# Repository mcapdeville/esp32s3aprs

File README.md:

# ESP32s3APRS

The ESP32s3APRS project aims to develop an open-source APRS (Automatic Packet Reporting System) beacon/tracker/logger, USB kiss TNC , USB audio FM tranceiver with Micropython shell based on the ESP32-S3 microcontroller.

## Project Overview

The ESP32s3APRS is a comprehensive solution that combines hardware and software components to create a versatile packet radio. The main features include:

- **APRS and AX.25 Capabilities**: The device can transmit and receive APRS and AX.25 frames, allowing for bidirectional communication over radio.
- **USB Connectivity**: The tracker connects to a computer via USB, providing two CDC-ACM ports:
  - One port for a TNC KISS protocol interface
  - One port for a MicroPython console
- **UAC2 Audio Support**: The USB implementation includes the UAC2 protocol, enabling direct audio streaming between the device and the computer.
- **GPS**: Integrated GPS with embeded antenna.
- **Sensor Integration**: The tracker can integrate various sensors, to enrich the data transmitted over the APRS network.
- **USB-C battery charger**: can accept power input from 5v to 14V 
- **User Interface**: The device features an e-paper display and three buttons for configuration and control.
- **Power Management**: The system is designed for low power consumption, allowing for extended autonomous operation.

## Hardware Components

The ESP32s3APRS hardware consists of the following main components:

- ESP32-S3 microcontroller
- SA868 radio module
- Quectel L86 GPS receiver
- E-paper display
- 3 buttons
- USB-C battery charger

The schematic and PCB are designed with Kicad (https://www.kicad.org).
The hardware design files are distributed under the CERN-OHL-S v2 license (or later)

## Software

The software for the ESP32s3APRS is released under the GPL v3 (or later) license. It includes:

- Embedded firmware for the ESP32-S3
- APRS and AX.25 frame processing
- Data storage in flash memory
- Configuration via the user interface and MicroPython console

## Getting Started

To get started with the ESP32s3APRS project, please follow these steps:

1. Clone the repository: `git clone https://github.com/mcapdeville/esp32s3aprs.git`
2. Change to project directory: cd esp32s3aprs
3. Initialize submodules : ./init.sh

## Compile

From the project directory :

1. Load the environment variables: . ./esp-idf/export.sh
2. Compile the project: idf.py build

## Flash the device

1. Put the switch on 'Boot' position
2. Connect USB cable
3. Run: idf.py flash

## Contributing

The ESP32s3APRS project welcomes contributions from the community. You can contribute by:

- Reporting bugs or issues
- Suggesting new features or improvements
- Submitting pull requests for code or documentation changes

## License

The ESP32s3APRS software is licensed under the GPL v3 (or later) license.
The hardware design files are licensed under the CERN-OHL-S v2 license.
See the `LICENSE-GPL-V3.txt` and `LICENSE-CERN-OHL-S-V2.txt` files for more details.

## Acknowledgments

The ESP32s3APRS project was created by Marc CAPDEVILLE (F4JMZ).

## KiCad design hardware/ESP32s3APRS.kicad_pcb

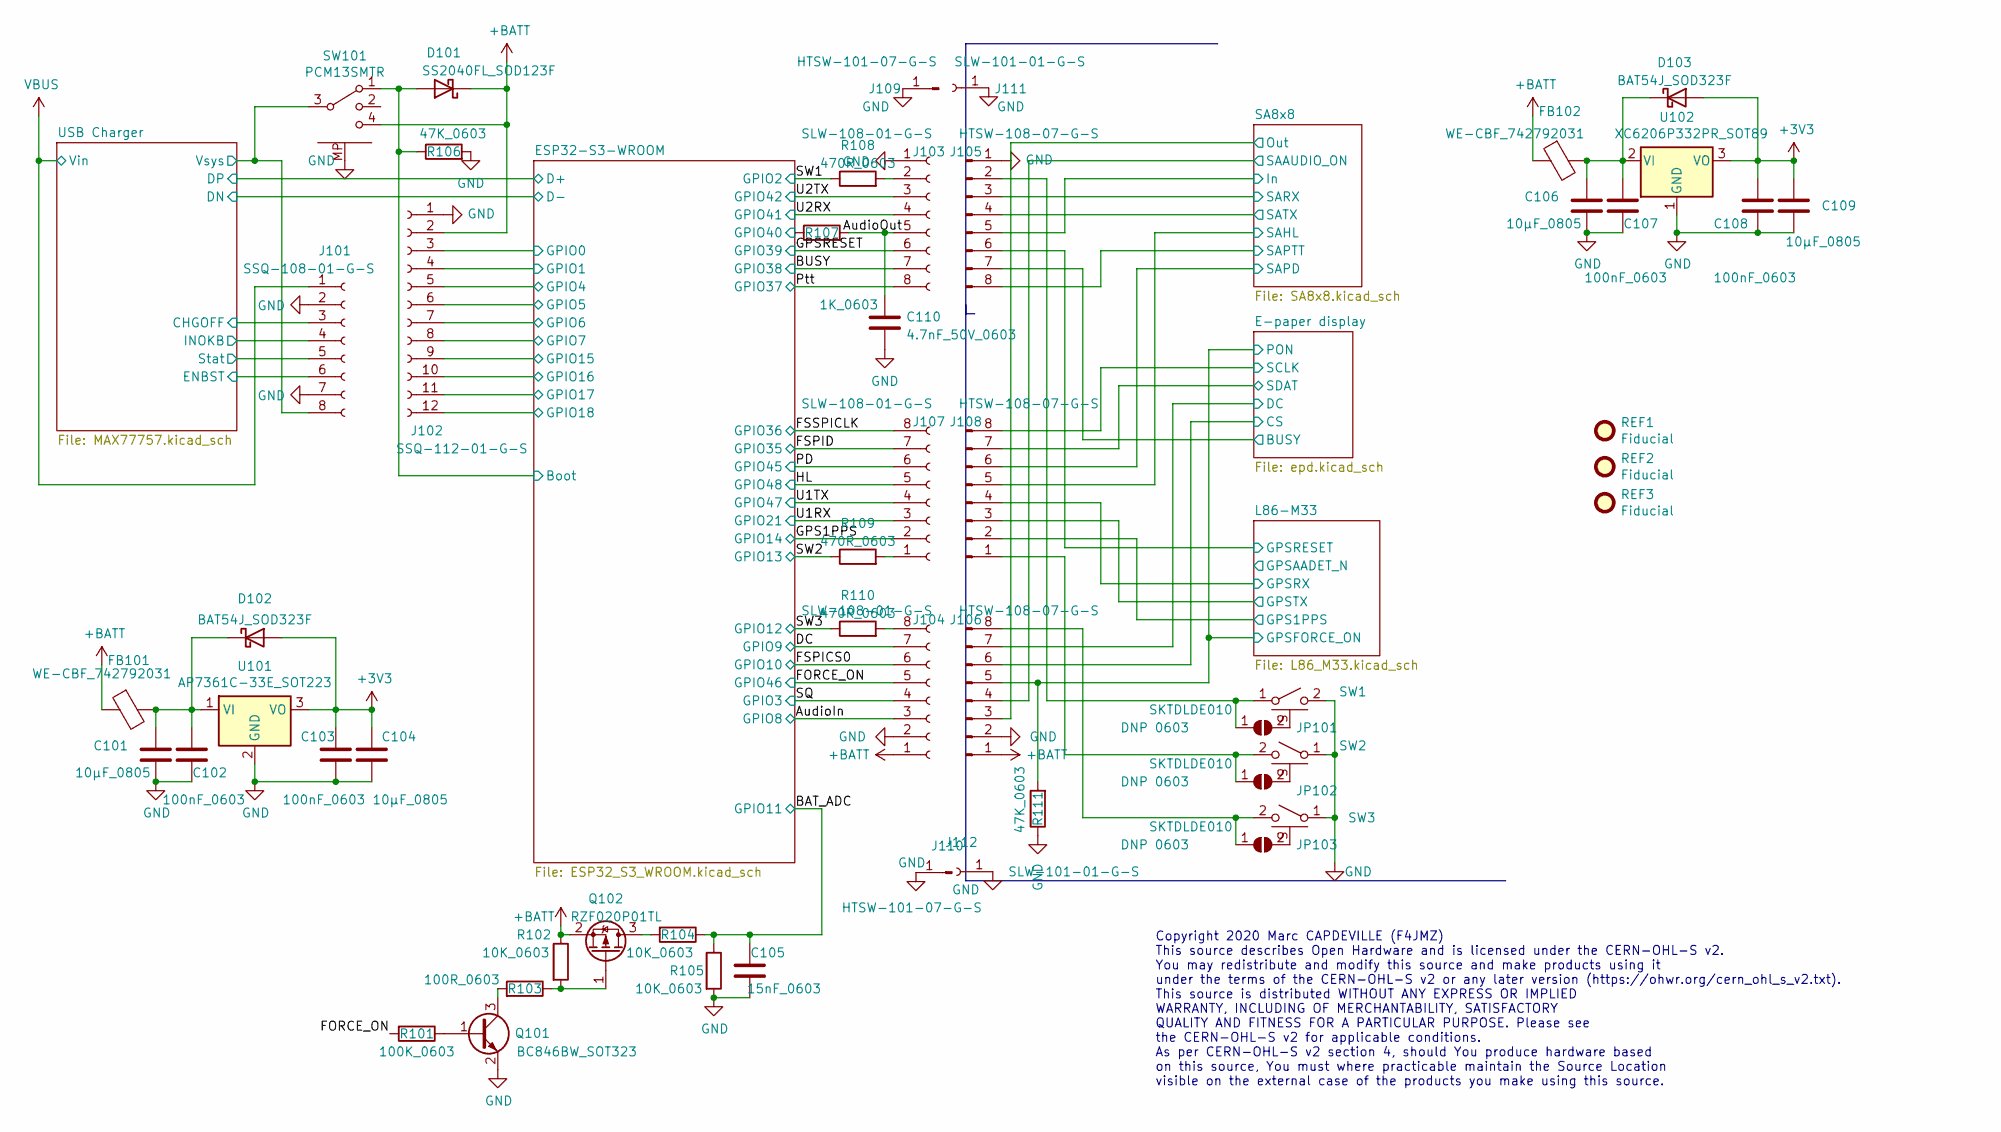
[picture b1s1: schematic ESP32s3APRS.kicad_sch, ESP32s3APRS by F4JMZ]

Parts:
C101, C104, C106, C109: 10µF_0805; C_0805_2012Metric; Mouser 963-TMK212BBJ106MG-T
C102, C103, C107, C108: 100nF_0603; C_0603_1608Metric; Mouser 963-UMK107B7104KAHT
C105: 15nF_0603; C_0603_1608Metric; Mouser 710-885012206090
C110: 4.7nF_50V_0603; C_0603_1608Metric; Mouser 80-C0603C472K5R
D101: SS2040FL_SOD123F; D_SOD-123F; Mouser 241-SS2040FLAUR100A1
D102, D103: BAT54J_SOD323F; D_SOD-323F; Mouser 771-BAT54J115
FB101, FB102: WE-CBF_742792031; L_0805_2012Metric; Mouser 710-742792031
J101: SSQ-108-01-G-S; PinSocket_1x08_P2.54mm_Vertical; Mouser 200-SSQ10801GS
J102: SSQ-112-01-G-S; PinSocket_1x12_P2.54mm_Vertical; Mouser 200-SSQ11201GS
J103, J104, J107: SLW-108-01-G-S; PinSocket_1x08_P2.54mm_Vertical; Mouser 200-SLW10801GS
J105, J106, J108: HTSW-108-07-G-S; PinHeader_1x08_P2.54mm_Vertical; Mouser 200-HTSW10807GS
J109, J110: HTSW-101-07-G-S; PinHeader_1x01_P2.54mm_Vertical; Mouser 200-HTSW10107GS
J111, J112: SLW-101-01-G-S; PinSocket_1x01_P2.54mm_Vertical; Mouser 200-SLW10101GS
JP101, JP102, JP103: DNP 0603; R_0603_1608Metric_Pad0.98x0.95mm_HandSolder
Q101: BC846BW_SOT323; SOT-323_SC-70; Mouser 771-BC846BW-T/R
Q102: RZF020P01TL; SOT-323T_SC-113A; Mouser 755-RZF020P01TL
R101: 100K_0603; R_0603_1608Metric; Mouser 603-RC0603FR-07100KL
R102, R104, R105: 10K_0603; R_0603_1608Metric; Mouser 603-RC0603FR-0710KL
R103: 100R_0603; R_0603_1608Metric; Mouser 603-RC0603FR-07100RL
R106, R111: 47K_0603; R_0603_1608Metric; Mouser 603-RC0603FR-0747KL
R107: 1K_0603; R_0603_1608Metric; Mouser 603-RC0603FR-071KL
R108, R109, R110: 470R_0603; R_0603_1608Metric
REF1, REF2, REF3: Fiducial; Fiducial_0.75mm_Mask1.5mm
SW1, SW2, SW3: SKTDLDE010; Mouser 688-SKTDLDE010
SW101: PCM13SMTR; SW_PCM13SMTR _SP3T; Mouser 611-PCM13SMTR
U101: AP7361C-33E_SOT223; SOT-223-3_TabPin2; Mouser 621-AP7361C-33E-13
U102: XC6206P332PR_SOT89; SOT-89-3; Mouser 865-XC6206P332PR-G

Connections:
+3V3: C103.1, C104.1, C108.1, C109.1, D102.2 (A), D103.2 (A), U101.3 (VO), U102.3 (VO); also elsewhere on the board
+BATT: D101.1 (K), FB101.1, FB102.1, J102.2, J104.1, J106.1, Q102.2 (S), R102.1, SW101.4; also elsewhere on the board
/AudioIn: J104.3; also elsewhere on the board
/BAT_ADC: C105.1, R104.1, R105.1; also elsewhere on the board
/BUSY: J103.7; also elsewhere on the board
/DC: J104.7; also elsewhere on the board
/E-paper display/BUSY: J105.7; also elsewhere on the board
/E-paper display/CS: J106.6; also elsewhere on the board
/E-paper display/DC: J106.7; also elsewhere on the board
/E-paper display/PON: J106.5, R111.2; also elsewhere on the board
/E-paper display/SCLK: J108.8; also elsewhere on the board
/E-paper display/SDAT: J108.7; also elsewhere on the board
/ESP32-S3-WROOM/Boot: D101.2 (A), R106.1, SW101.1; also elsewhere on the board
/ESP32-S3-WROOM/GPIO0: J102.3; also elsewhere on the board
/ESP32-S3-WROOM/GPIO1: J102.4; also elsewhere on the board
/ESP32-S3-WROOM/GPIO4: J102.5; also elsewhere on the board
/ESP32-S3-WROOM/GPIO5: J102.6; also elsewhere on the board
/ESP32-S3-WROOM/GPIO6: J102.7; also elsewhere on the board
/ESP32-S3-WROOM/GPIO7: J102.8; also elsewhere on the board
/ESP32-S3-WROOM/GPIO15: J102.9; also elsewhere on the board
/ESP32-S3-WROOM/GPIO16: J102.10; also elsewhere on the board
/ESP32-S3-WROOM/GPIO17: J102.11; also elsewhere on the board
/ESP32-S3-WROOM/GPIO18: J102.12; also elsewhere on the board
/ESP32-S3-WROOM/GPIO40: R107.1; also elsewhere on the board
/FORCE_ON: J104.5, R101.2; also elsewhere on the board
/FSPICS0: J104.6; also elsewhere on the board
/FSPID: J107.7; also elsewhere on the board
/FSSPICLK: J107.8; also elsewhere on the board
/GPS1PPS: J107.2; also elsewhere on the board
/GPSRESET: J103.6; also elsewhere on the board
/HL: J107.5; also elsewhere on the board
/L86-M33/GPS1PPS: J108.2; also elsewhere on the board
/L86-M33/GPSRESET: J105.6; also elsewhere on the board
/L86-M33/GPSRX: J108.4; also elsewhere on the board
/L86-M33/GPSTX: J108.3; also elsewhere on the board
/PD: J107.6; also elsewhere on the board
/Ptt: J103.8; also elsewhere on the board
/SA8x8/In: J105.5; also elsewhere on the board
/SA8x8/Out: J106.3; also elsewhere on the board
/SA8x8/SAAUDIO_ON: J106.4; also elsewhere on the board
/SA8x8/SAHL: J108.5; also elsewhere on the board
/SA8x8/SAPD: J108.6; also elsewhere on the board
/SA8x8/SAPTT: J105.8; also elsewhere on the board
/SA8x8/SARX: J105.3; also elsewhere on the board
/SA8x8/SATX: J105.4; also elsewhere on the board
/SQ: J104.4; also elsewhere on the board
/SW1: R108.1; also elsewhere on the board
/SW2: R109.1; also elsewhere on the board
/SW3: R110.1; also elsewhere on the board
/U1RX: J107.3; also elsewhere on the board
/U1TX: J107.4; also elsewhere on the board
/U2RX: J103.4; also elsewhere on the board
/U2TX: J103.3; also elsewhere on the board
/USB Charger/CHGOFF: J101.3; also elsewhere on the board
/USB Charger/ENBST: J101.6; also elsewhere on the board
/USB Charger/INOKB: J101.4; also elsewhere on the board
/USB Charger/Stat: J101.5; also elsewhere on the board
/USB Charger/Vsys: J101.8, SW101.3; also elsewhere on the board
GND: C101.2, C102.2, C103.2, C104.2, C105.2, C106.2, C107.2, C108.2, C109.2, C110.2, J101.2, J101.7, J102.1, J103.1, J104.2, J105.1, J106.2, J109.1, J110.1, J111.1, J112.1, Q101.2 (E), R105.2, R106.2, R111.1, SW1.2 (B), SW2.1 (A), SW3.1 (A), SW101.MP, U101.2 (GND), U102.1 (GND); also elsewhere on the board
unnamed: C101.1, C102.1, D102.1 (K), FB101.2, U101.1 (VI)
unnamed: C106.1, C107.1, D103.1 (K), FB102.2, U102.2 (VI)
unnamed: C110.1, J103.5, R107.2
unnamed: J103.2, R108.2
unnamed: J104.8, R110.2
unnamed: J105.2, JP101.1 (A), SW1.1 (A)
unnamed: J106.8, JP103.1 (A), SW3.2 (B)
unnamed: J107.1, R109.2
unnamed: J108.1, JP102.1 (A), SW2.2 (B)
unnamed: JP101.2 (B), SW1.S (MP)
unnamed: JP102.2 (B), SW2.S (MP)
unnamed: JP103.2 (B), SW3.S (MP)
unnamed: Q101.1 (B), R101.1
unnamed: Q101.3 (C), R103.2
unnamed: Q102.1 (G), R102.2, R103.1
unnamed: Q102.3 (D), R104.2
VBUS: J101.1; also elsewhere on the board

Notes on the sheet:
Copyright 2020 Marc CAPDEVILLE (F4JMZ) This source describes Open Hardware and is licensed under the CERN-OHL-S v2. You may redistribute and modify this source and make products using it under the terms of the CERN-OHL-S v2 or any later version (https://ohwr.org/cern_ohl_s_v2.txt). This source is d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

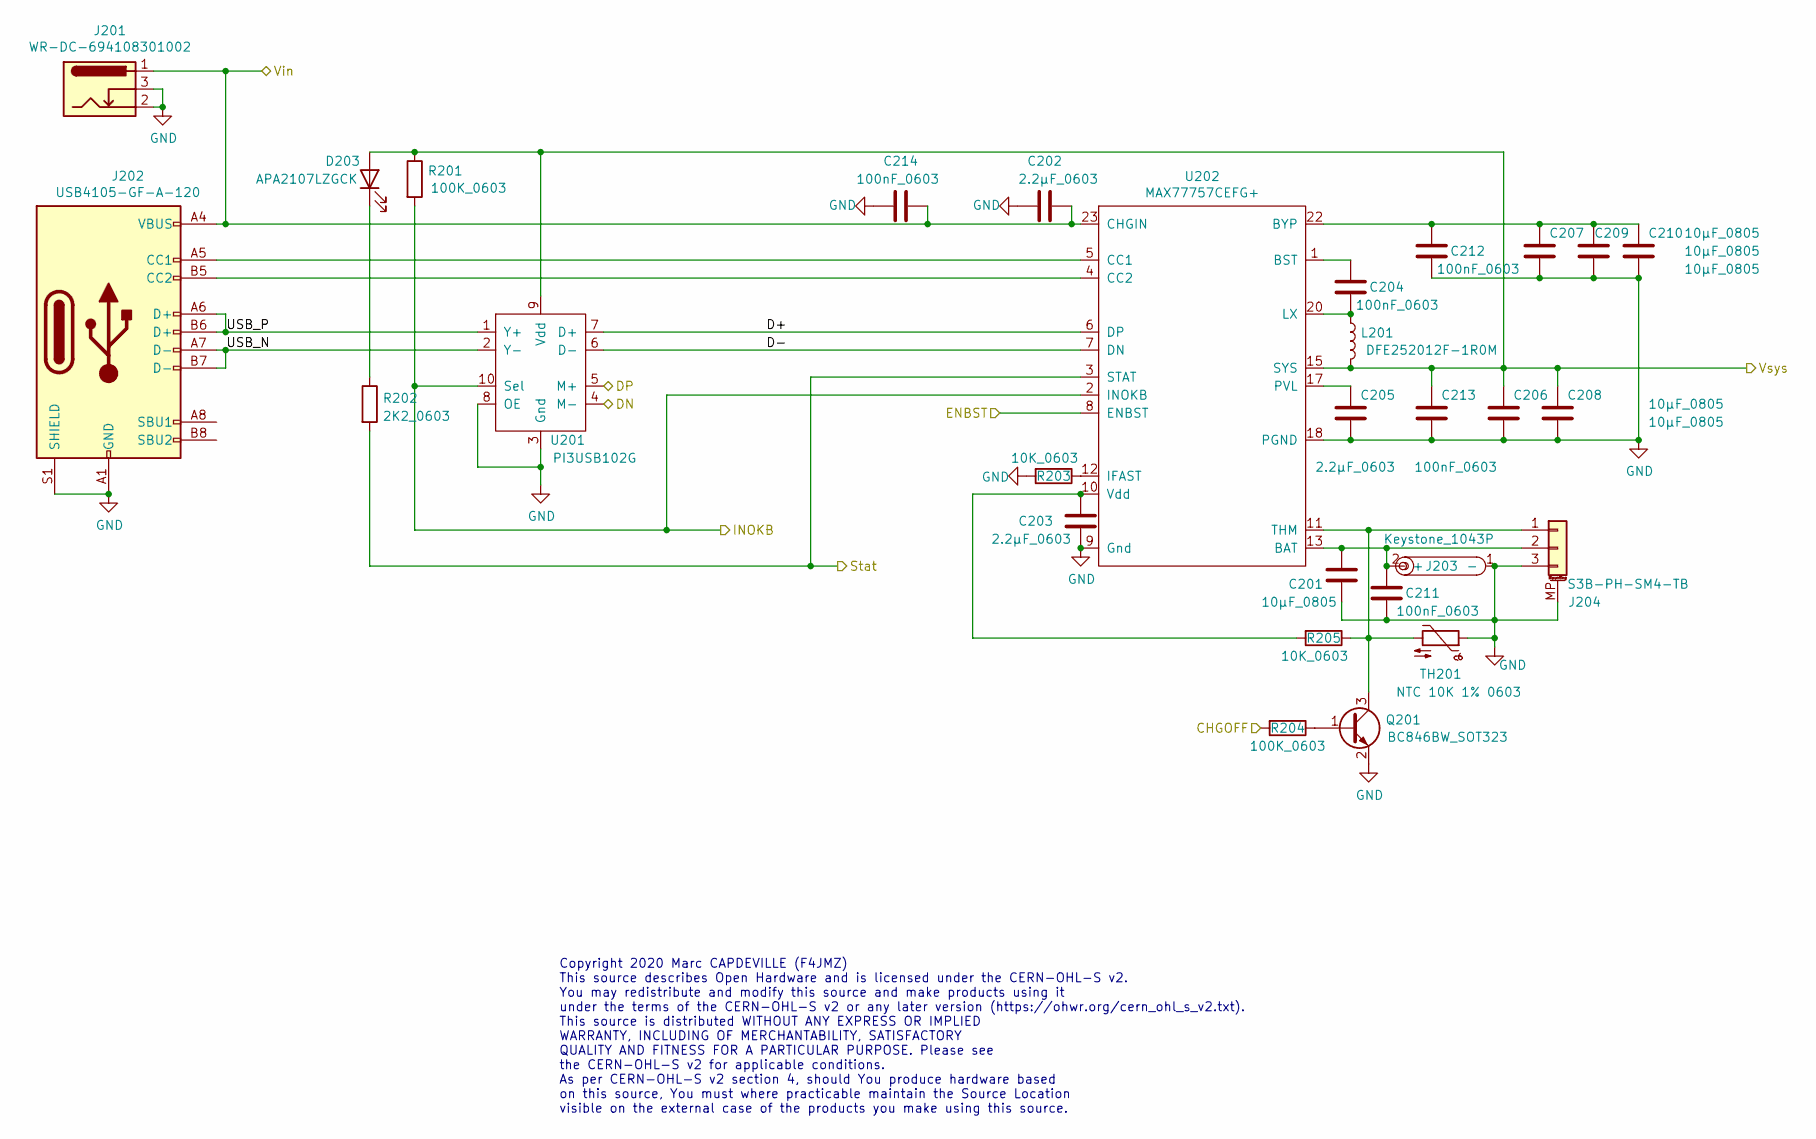
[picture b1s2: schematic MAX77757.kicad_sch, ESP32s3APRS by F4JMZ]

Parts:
C201, C206, C207, C208, C209, C210: 10µF_0805; C_0805_2012Metric; Mouser 963-TMK212BBJ106MG-T
C202, C203, C205: 2.2µF_0603; C_0603_1608Metric; Mouser 963-UMK107BBJ225KA-T
C204, C211, C212, C213, C214: 100nF_0603; C_0603_1608Metric; Mouser 963-UMK107B7104KAHT
D203: APA2107LZGCK; SIDELED_APA2107; Mouser 604-APA2107LZGCK
J201: WR-DC-694108301002; BarrelJack_Wuerth_6941xx301002; Mouser 710-694108301002
J202: USB4105-GF-A-120; USB_C_Receptacle_GCT_4105; Mouser 640-USB4105-GF-A-120
J203: Keystone_1043P; Keystone-1043; Mouser 534-1043
J204: S3B-PH-SM4-TB; JST_PH_S3B-PH-SM4-TB_1x03-1MP_P2.00mm_Horizontal; Mouser 306-S3BPHSM4TBLFSN
L201: DFE252012F-1R0M; L_1008_2520Metric; Mouser 81-DFE252012F-1R0MP2
Q201: BC846BW_SOT323; SOT-323_SC-70; Mouser 771-BC846BW-T/R
R201, R204: 100K_0603; R_0603_1608Metric; Mouser 603-RC0603FR-07100KL
R202: 2K2_0603; R_0603_1608Metric; Mouser 603-RC0603FR-072K2L
R203, R205: 10K_0603; R_0603_1608Metric; Mouser 603-RC0603FR-0710KL
TH201: NTC 10K 1% 0603; R_0603_1608Metric; Mouser 594-NTCS0603E3103FMT
U201: PI3USB102G; TQFN-10_1.3x1.6mm_P0.4mm; Mouser 729-PI3USB102GZLEX
U202: MAX77757CEFG+; FC2QFN-24_3x3_Pitch0.4mm; Mouser 700-MAX77757JEFG420

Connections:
/ESP32-S3-WROOM/D+: U201.5 (M+); also elsewhere on the board
/ESP32-S3-WROOM/D-: U201.4 (M-); also elsewhere on the board
/USB Charger/CHGOFF: R204.2; also elsewhere on the board
/USB Charger/D+: U201.7 (D+), U202.6 (DP)
/USB Charger/D-: U201.6 (D-), U202.7 (DN)
/USB Charger/ENBST: U202.8 (ENBST); also elsewhere on the board
/USB Charger/INOKB: R201.2, U201.10 (Sel), U202.2 (INOKB); also elsewhere on the board
/USB Charger/Stat: R202.2, U202.3 (STAT); also elsewhere on the board
/USB Charger/USB_N: J202.A7 (D-), J202.B7 (D-), U201.2 (Y-)
/USB Charger/USB_P: J202.A6 (D+), J202.B6 (D+), U201.1 (Y+)
/USB Charger/Vsys: C206.1, C208.1, C213.1, D203.2 (A), L201.2, R201.1, U201.9 (Vdd), U202.15 (SYS), U202.16 (SYS); also elsewhere on the board
GND: C201.2, C202.2, C203.2, C205.2, C206.2, C207.2, C208.2, C209.2, C210.2, C211.2, C212.2, C213.2, C214.2, J201.2, J201.3, J202.A1 (GND), J202.A12 (GND), J202.B1 (GND), J202.B12 (GND), J202.S1 (SHIELD), J203.1 (-), J204.3, J204.MP (MountPin), Q201.2 (E), R203.2, TH201.1, U201.3 (Gnd), U201.8 (OE), U202.9 (Gnd), U202.18 (PGND), U202.19 (PGND); also elsewhere on the board
unnamed: C201.1, C211.1, J203.2 (+), J204.2, U202.13 (BAT), U202.14 (BAT)
unnamed: C203.1, R205.2, U202.10 (Vdd)
unnamed: C204.1, U202.1 (BST)
unnamed: C204.2, L201.1, U202.20 (LX), U202.21 (LX)
unnamed: C205.1, U202.17 (PVL)
unnamed: C207.1, C209.1, C210.1, C212.1, U202.22 (BYP)
unnamed: D203.1 (K), R202.1
unnamed: J202.A5 (CC1), U202.5 (CC1)
unnamed: J202.B5 (CC2), U202.4 (CC2)
unnamed: J204.1, Q201.3 (C), R205.1, TH201.2, U202.11 (THM)
unnamed: Q201.1 (B), R204.1
unnamed: R203.1, U202.12 (IFAST)
VBUS: C202.1, C214.1, J201.1, J202.A4 (VBUS), J202.A9 (VBUS), J202.B4 (VBUS), J202.B9 (VBUS), U202.23 (CHGIN), U202.24 (CHGIN); also elsewhere on the board

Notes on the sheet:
Copyright 2020 Marc CAPDEVILLE (F4JMZ) This source describes Open Hardware and is licensed under the CERN-OHL-S v2. You may redistribute and modify this source and make products using it under the terms of the CERN-OHL-S v2 or any later version (https://ohwr.org/cern_ohl_s_v2.txt). This source is d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

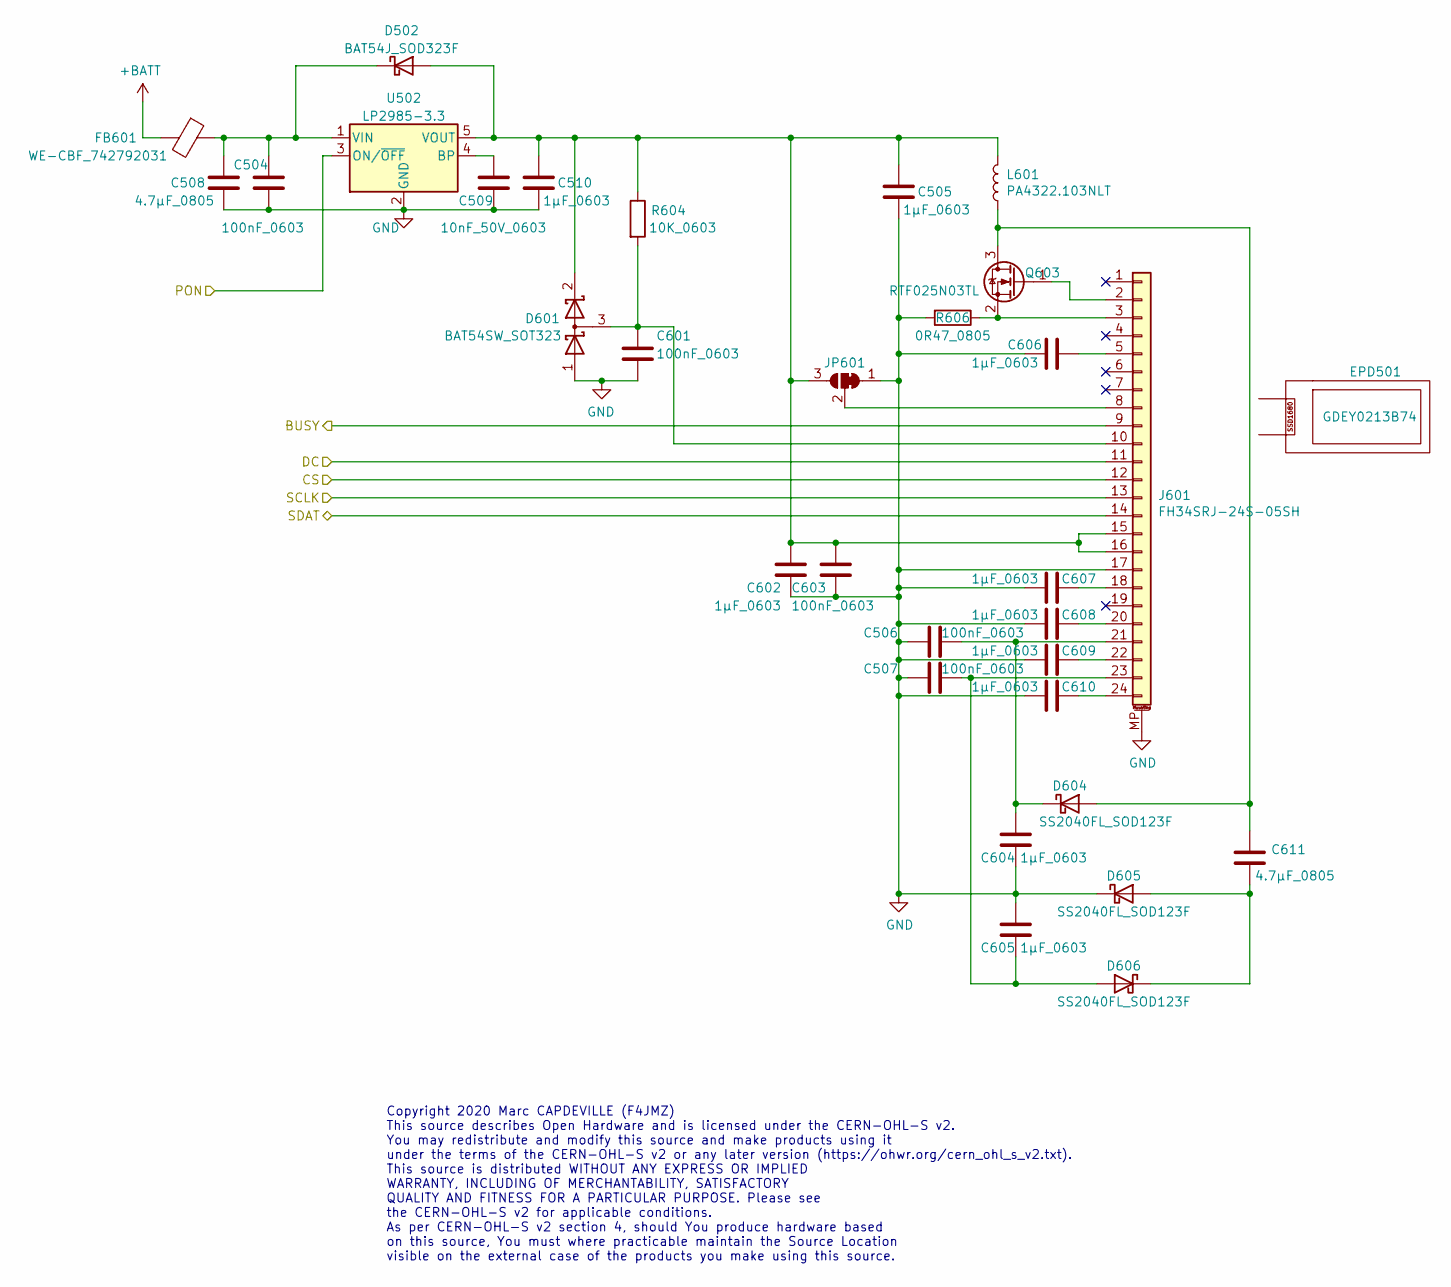
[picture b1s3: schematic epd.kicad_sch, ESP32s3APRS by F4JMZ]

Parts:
C504, C506, C507, C601, C603: 100nF_0603; C_0603_1608Metric; Mouser 963-UMK107B7104KAHT
C505, C510, C602, C604, C605, C606, C607, C608, C609, C610: 1µF_0603; C_0603_1608Metric; Mouser 963-UMK107BJ105KA-T
C508, C611: 4.7µF_0805; C_0805_2012Metric; Mouser 81-GRM21BR61H475KE1L
C509: 10nF_50V_0603; C_0603_1608Metric
D502: BAT54J_SOD323F; D_SOD-323F; Mouser 771-BAT54J115
D601: BAT54SW_SOT323; SOT-323_SC-70; Mouser 771-BAT54SW-T/R
D604, D605, D606: SS2040FL_SOD123F; D_SOD-123F; Mouser 241-SS2040FLAUR100A1
EPD501: GDEY0213B74; GDEY0213B74_2.13_EPD
FB601: WE-CBF_742792031; L_0805_2012Metric; Mouser 710-742792031
J601: FH34SRJ-24S-05SH; Hirose_FH34-24SRJ-0.5SH_1x24-1MP_P0.50mm_Horizontal; Mouser 798-FH34SRJ24S05SH99
JP601: SolderJumper_3_Bridged12; SolderJumper-3_P1.3mm_Bridged2Bar12_Pad1.0x1.5mm_NumberLabe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
L601: PA4322.103NLT; Inductor_Pulse_PA4322.xxxNLT_5.1x5.1; Mouser 673-PA4322.103NLT
Q603: RTF025N03TL; SOT-323T_SC-113A; Mouser 755-RTF025N03TL
R604: 10K_0603; R_0603_1608Metric; Mouser 603-RC0603FR-0710KL
R606: 0R47_0805; R_0805_2012Metric; Mouser 71-RCWE0805R470FKEA
U502: LP2985-3.3; SOT-23-5

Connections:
+BATT: FB601.2; also elsewhere on the board
/E-paper display/BUSY: J601.9; also elsewhere on the board
/E-paper display/CS: J601.12; also elsewhere on the board
/E-paper display/DC: J601.11; also elsewhere on the board
/E-paper display/PON: U502.3 (ON/~OFF); also elsewhere on the board
/E-paper display/SCLK: J601.13; also elsewhere on the board
/E-paper display/SDAT: J601.14; also elsewhere on the board
GND: C504.1, C505.1, C506.1, C507.1, C508.2, C509.2, C510.1, C601.2, C602.1, C603.2, C604.1, C605.2, C606.2, C607.2, C608.2, C609.2, C610.2, D601.1 (A), D605.1 (K), J601.17, J601.MP (MountPin), JP601.1 (A), R606.2, U502.2 (GND); also elsewhere on the board
unnamed: C504.2, C508.1, D502.1 (K), FB601.1, U502.1 (VIN)
unnamed: C505.2, C510.2, C602.2, C603.1, D502.2 (A), D601.2 (A), J601.15, J601.16, JP601.3 (B), L601.2, R604.1, U502.5 (VOUT)
unnamed: C506.2, C604.2, D604.1 (K), J601.21
unnamed: C507.2, C605.1, D606.2 (A), J601.23
unnamed: C509.1, U502.4 (BP)
unnamed: C601.1, D601.3 (K), J601.10, R604.2
unnamed: C606.1, J601.5
unnamed: C607.1, J601.18
unnamed: C608.1, J601.20
unnamed: C609.1, J601.22
unnamed: C610.1, J601.24
unnamed: C611.1, D604.2 (A), L601.1, Q603.3 (D)
unnamed: C611.2, D605.2 (A), D606.1 (K)
unnamed: J601.2, Q603.1 (G)
unnamed: J601.3, Q603.2 (S), R606.1
unnamed: J601.8, JP601.2 (C)

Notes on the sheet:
Copyright 2020 Marc CAPDEVILLE (F4JMZ) This source describes Open Hardware and is licensed under the CERN-OHL-S v2. You may redistribute and modify this source and make products using it under the terms of the CERN-OHL-S v2 or any later version (https://ohwr.org/cern_ohl_s_v2.txt). This source is d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

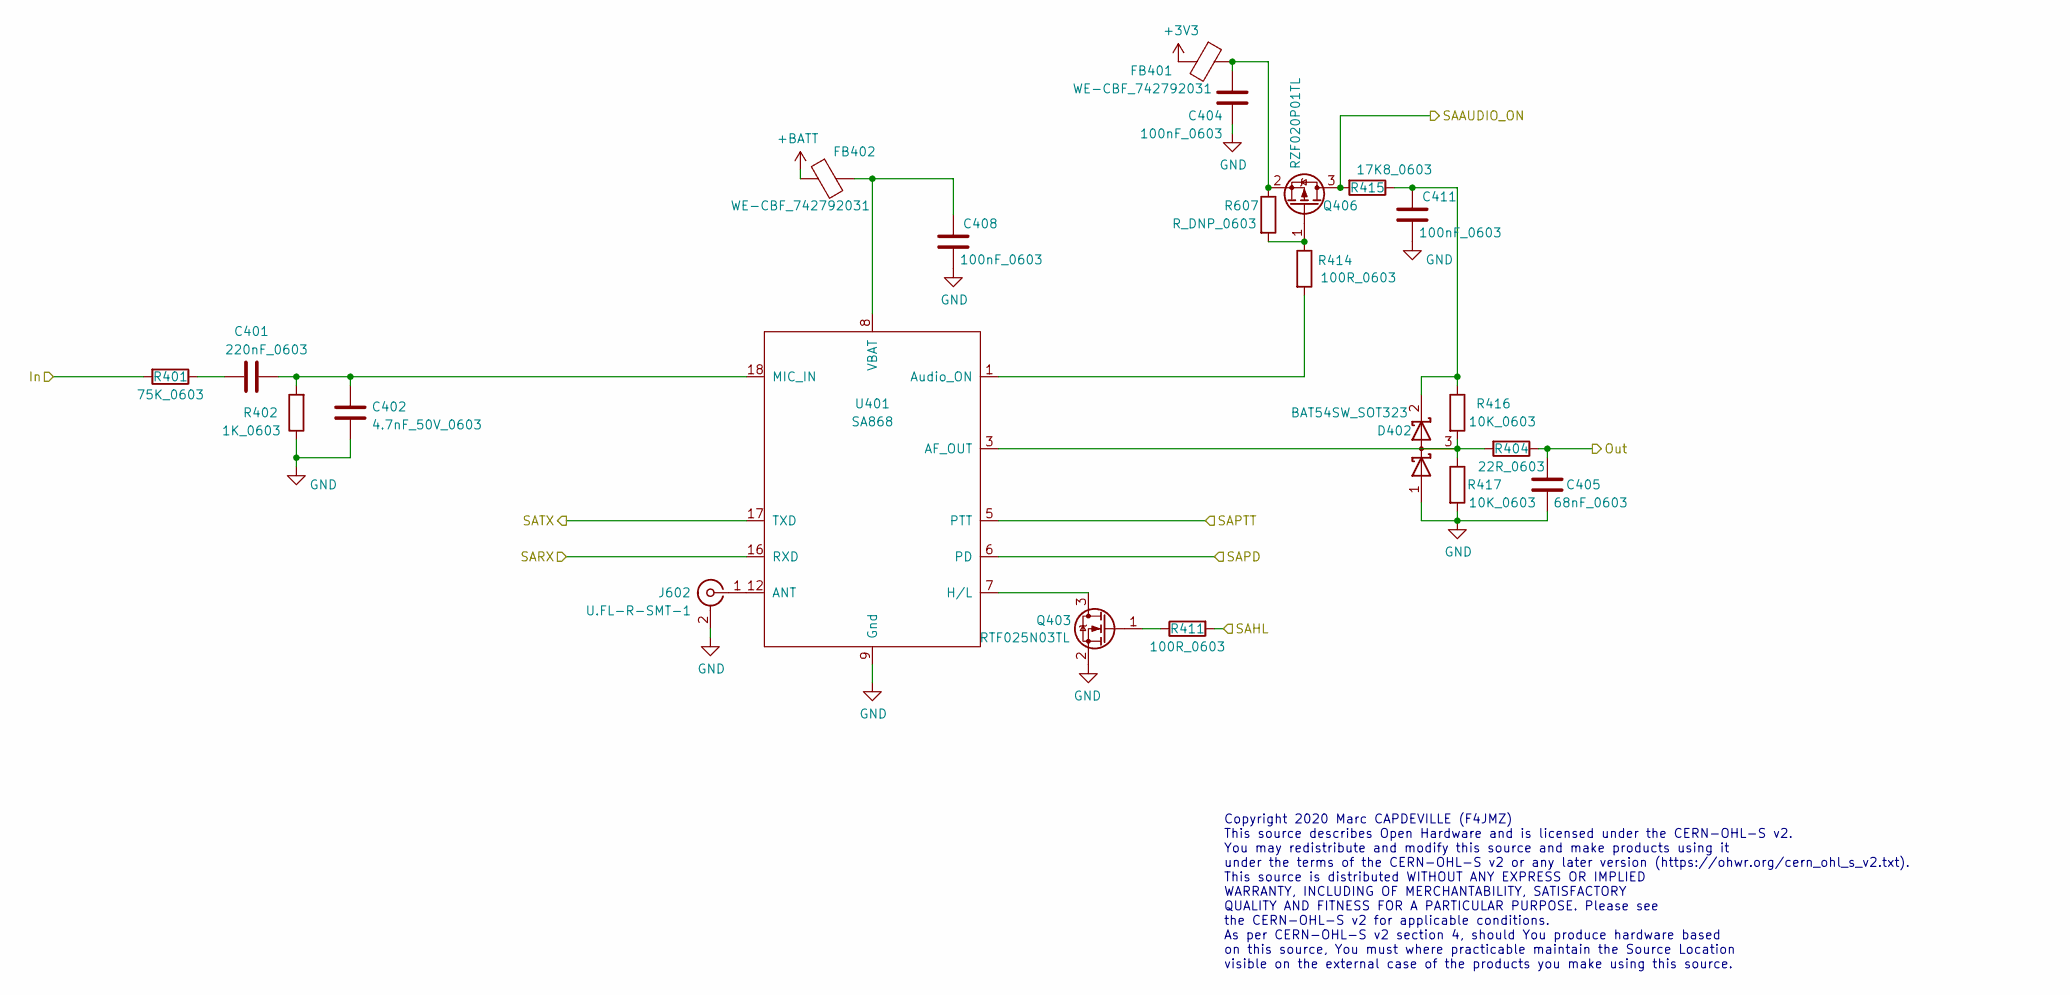
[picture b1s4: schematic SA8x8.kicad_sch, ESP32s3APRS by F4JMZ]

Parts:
C401: 220nF_0603; C_0603_1608Metric; Mouser 963-UMK107B7224KAHT
C402: 4.7nF_50V_0603; C_0603_1608Metric; Mouser 80-C0603C472K5R
C404, C408, C411: 100nF_0603; C_0603_1608Metric; Mouser 963-UMK107B7104KAHT
C405: 68nF_0603; C_0603_1608Metric; Mouser 710-885012206094
D402: BAT54SW_SOT323; SOT-323_SC-70; Mouser 771-BAT54SW-T/R
FB401, FB402: WE-CBF_742792031; L_0805_2012Metric; Mouser 710-742792031
J602: U.FL-R-SMT-1; U.FL_Hirose_U.FL-R-SMT-1_Vertical; Mouser 798-U.FL-R-SMT-110
Q403: RTF025N03TL; SOT-323T_SC-113A; Mouser 755-RTF025N03TL
Q406: RZF020P01TL; SOT-323T_SC-113A; Mouser 755-RZF020P01TL
R401: 75K_0603; R_0603_1608Metric; Mouser 603-RC0603FR-0775KL
R402: 1K_0603; R_0603_1608Metric; Mouser 603-RC0603FR-071KL
R404: 22R_0603; R_0603_1608Metric; Mouser 603-RC0603FR-0722RL
R411, R414: 100R_0603; R_0603_1608Metric; Mouser 603-RC0603FR-07100RL
R415: 17K8_0603; R_0603_1608Metric; Mouser 603-RC0603FR-0717K8L
R416, R417: 10K_0603; R_0603_1608Metric; Mouser 603-RC0603FR-0710KL
R607: R_DNP_0603; R_0603_1608Metric
U401: SA868; SA8x8

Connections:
+3V3: FB401.2; also elsewhere on the board
+BATT: FB402.1; also elsewhere on the board
/SA8x8/In: R401.2; also elsewhere on the board
/SA8x8/Out: C405.2, R404.1; also elsewhere on the board
/SA8x8/SAAUDIO_ON: Q406.3 (D), R415.2; also elsewhere on the board
/SA8x8/SAHL: R411.2; also elsewhere on the board
/SA8x8/SAPD: U401.6 (PD); also elsewhere on the board
/SA8x8/SAPTT: U401.5 (PTT); also elsewhere on the board
/SA8x8/SARX: U401.16 (RXD); also elsewhere on the board
/SA8x8/SATX: U401.17 (TXD); also elsewhere on the board
Diss: U401.21 (Diss)
Fix1: U401.20 (Fix1)
Fix2: U401.19 (Fix2)
GND: C402.2, C404.2, C405.1, C408.2, C411.1, D402.1 (A), J602.2 (Ext), Q403.2 (S), R402.1, R417.2, U401.9 (Gnd), U401.10 (Gnd); also elsewhere on the board
unnamed: C401.1, C402.1, R402.2, U401.18 (MIC_IN)
unnamed: C401.2, R401.1
unnamed: C404.1, FB401.1, Q406.2 (S), R607.1
unnamed: C408.1, FB402.2, U401.8 (VBAT)
unnamed: C411.2, D402.2 (A), R415.1, R416.1
unnamed: D402.3 (K), R404.2, R416.2, R417.1, U401.3 (AF_OUT)
unnamed: J602.1 (In), U401.12 (ANT)
unnamed: Q403.1 (G), R411.1
unnamed: Q403.3 (D), U401.7 (H/L)
unnamed: Q406.1 (G), R414.1, R607.2
unnamed: R414.2, U401.1 (Audio_ON)

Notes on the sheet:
Copyright 2020 Marc CAPDEVILLE (F4JMZ) This source describes Open Hardware and is licensed under the CERN-OHL-S v2. You may redistribute and modify this source and make products using it under the terms of the CERN-OHL-S v2 or any later version (https://ohwr.org/cern_ohl_s_v2.txt). This source is d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

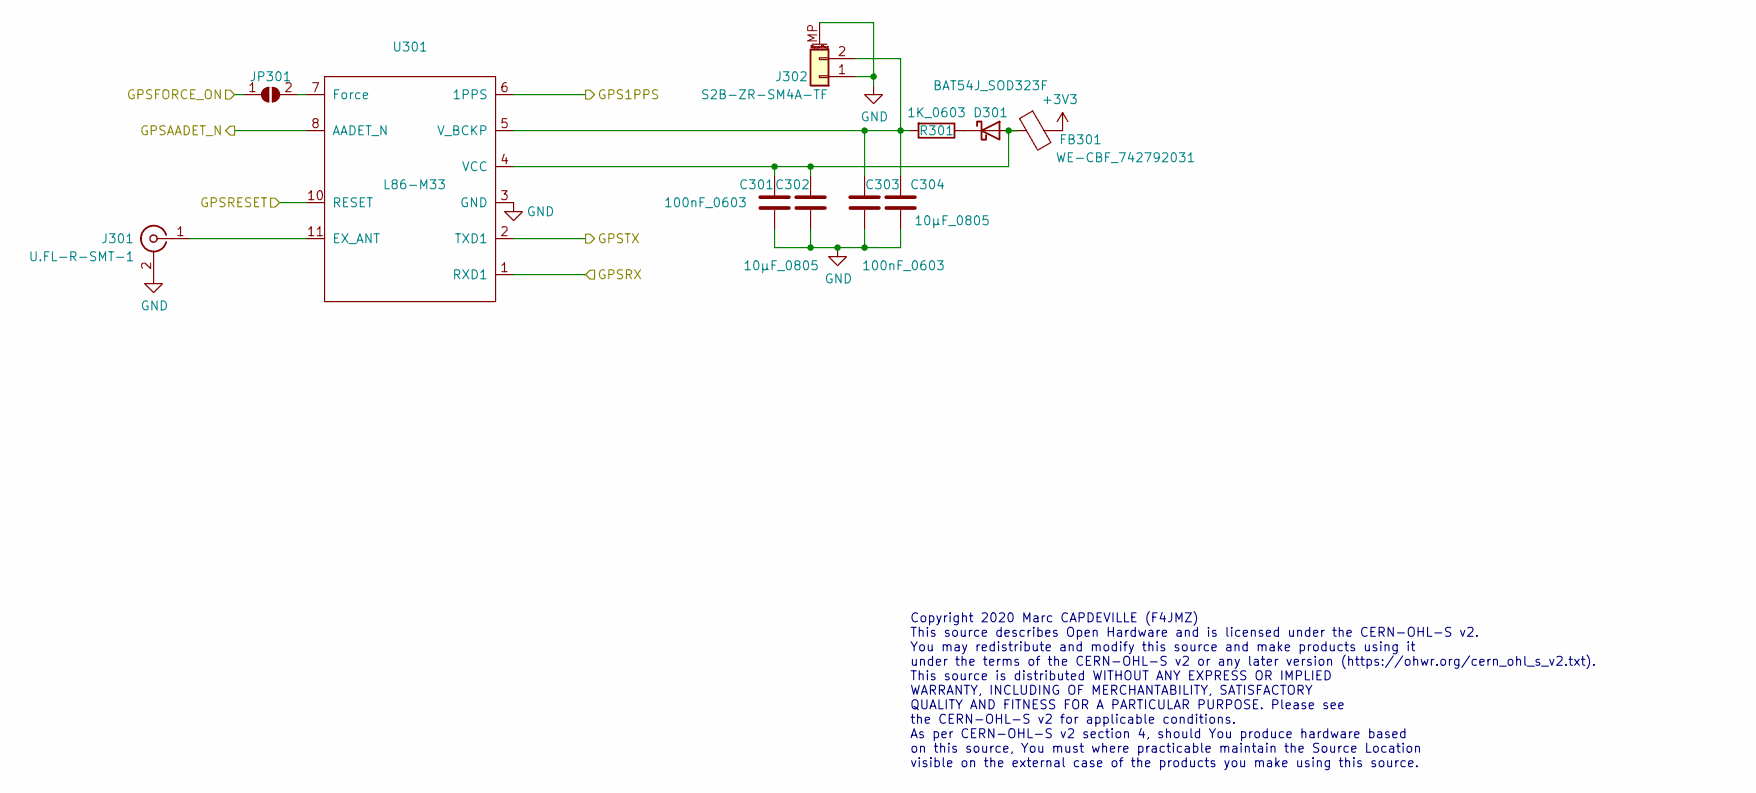
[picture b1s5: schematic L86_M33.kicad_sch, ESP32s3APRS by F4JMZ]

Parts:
C301, C303: 100nF_0603; C_0603_1608Metric; Mouser 963-UMK107B7104KAHT
C302, C304: 10µF_0805; C_0805_2012Metric; Mouser 963-TMK212BBJ106MG-T
D301: BAT54J_SOD323F; D_SOD-323F; Mouser 771-BAT54J115
FB301: WE-CBF_742792031; L_0805_2012Metric; Mouser 710-742792031
J301: U.FL-R-SMT-1; U.FL_Hirose_U.FL-R-SMT-1_Vertical; Mouser 798-U.FL-R-SMT-110
J302: S2B-ZR-SM4A-TF; JST_S2B-ZR-SM4A-TF_1x02-1MP_P1.50mm_Horizontal; Mouser 306-S2BZRSM4ATFLFSN
JP301: SolderJumper_2_Open; SolderJumper-2_P1.3mm_Open_RoundedPad1.0x1.5mm
R301: 1K_0603; R_0603_1608Metric; Mouser 603-RC0603FR-071KL
U301: L86-M33; XCVR_L86; Mouser 277-L86-M33

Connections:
+3V3: FB301.2; also elsewhere on the board
/E-paper display/PON: JP301.1 (A); also elsewhere on the board
/L86-M33/GPS1PPS: U301.6 (1PPS); also elsewhere on the board
/L86-M33/GPSAADET_N: U301.8 (AADET_N)
/L86-M33/GPSRESET: U301.10 (RESET); also elsewhere on the board
/L86-M33/GPSRX: U301.1 (RXD1); also elsewhere on the board
/L86-M33/GPSTX: U301.2 (TXD1); also elsewhere on the board
GND: C301.2, C302.2, C303.2, C304.2, J301.2 (Ext), J302.1, J302.MP (MountPin), U301.3 (GND), U301.12 (GND); also elsewhere on the board
unnamed: C301.1, C302.1, D301.2 (A), FB301.1, U301.4 (VCC)
unnamed: C303.1, C304.1, J302.2, R301.2, U301.5 (V_BCKP)
unnamed: D301.1 (K), R301.1
unnamed: J301.1 (In), U301.11 (EX_ANT)
unnamed: JP301.2 (B), U301.7 (Force)

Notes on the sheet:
Copyright 2020 Marc CAPDEVILLE (F4JMZ) This source describes Open Hardware and is licensed under the CERN-OHL-S v2. You may redistribute and modify this source and make products using it under the terms of the CERN-OHL-S v2 or any later version (https://ohwr.org/cern_ohl_s_v2.txt). This source is d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

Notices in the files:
hardware/ESP32_S3_WROOM.kicad_sch:
©️2025 Marc CAPDEVILLE (F4JMZ)
Licensed under CERN-OHL-S v2 (https://ohwr.org/cern_ohl_s_v2.txt)
QUALITY AND FITNESS FOR A PARTICULAR PURPOSE. Please see
the CERN-OHL-S v2 for applicable conditions.
As per CERN-OHL-S v2 section 4, should You produce hardware based
hardware/ESP32s3APRS.kicad_pcb:
Copyright 2025 Marc CAPDEVILLE (F4JMZ)
CERN-OHL-S v2
parts and their libraries:
Copyright: ©️2025 Marc CAPDEVILLE (F4JMZ)
License: Licensed under CERN-OHL-S v2 or any later version
